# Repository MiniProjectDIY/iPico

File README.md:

# iPico
RP2350 based UF2 hardware security key

## Hardware

iPico use the same IO as official raspberry pi Pico2 board, just replaced physical push button with capacitive touch button on pcb and change usb connector from female to male.

## Firmware
Use  [pico-fido](https://github.com/polhenarejos/pico-fido/releases) firmware for pico 2 board will do.

## Enclosure

3d printed case using file from 3D folder,using M1.4* 2 heat inserts and M1.4*5 counter sink screws.

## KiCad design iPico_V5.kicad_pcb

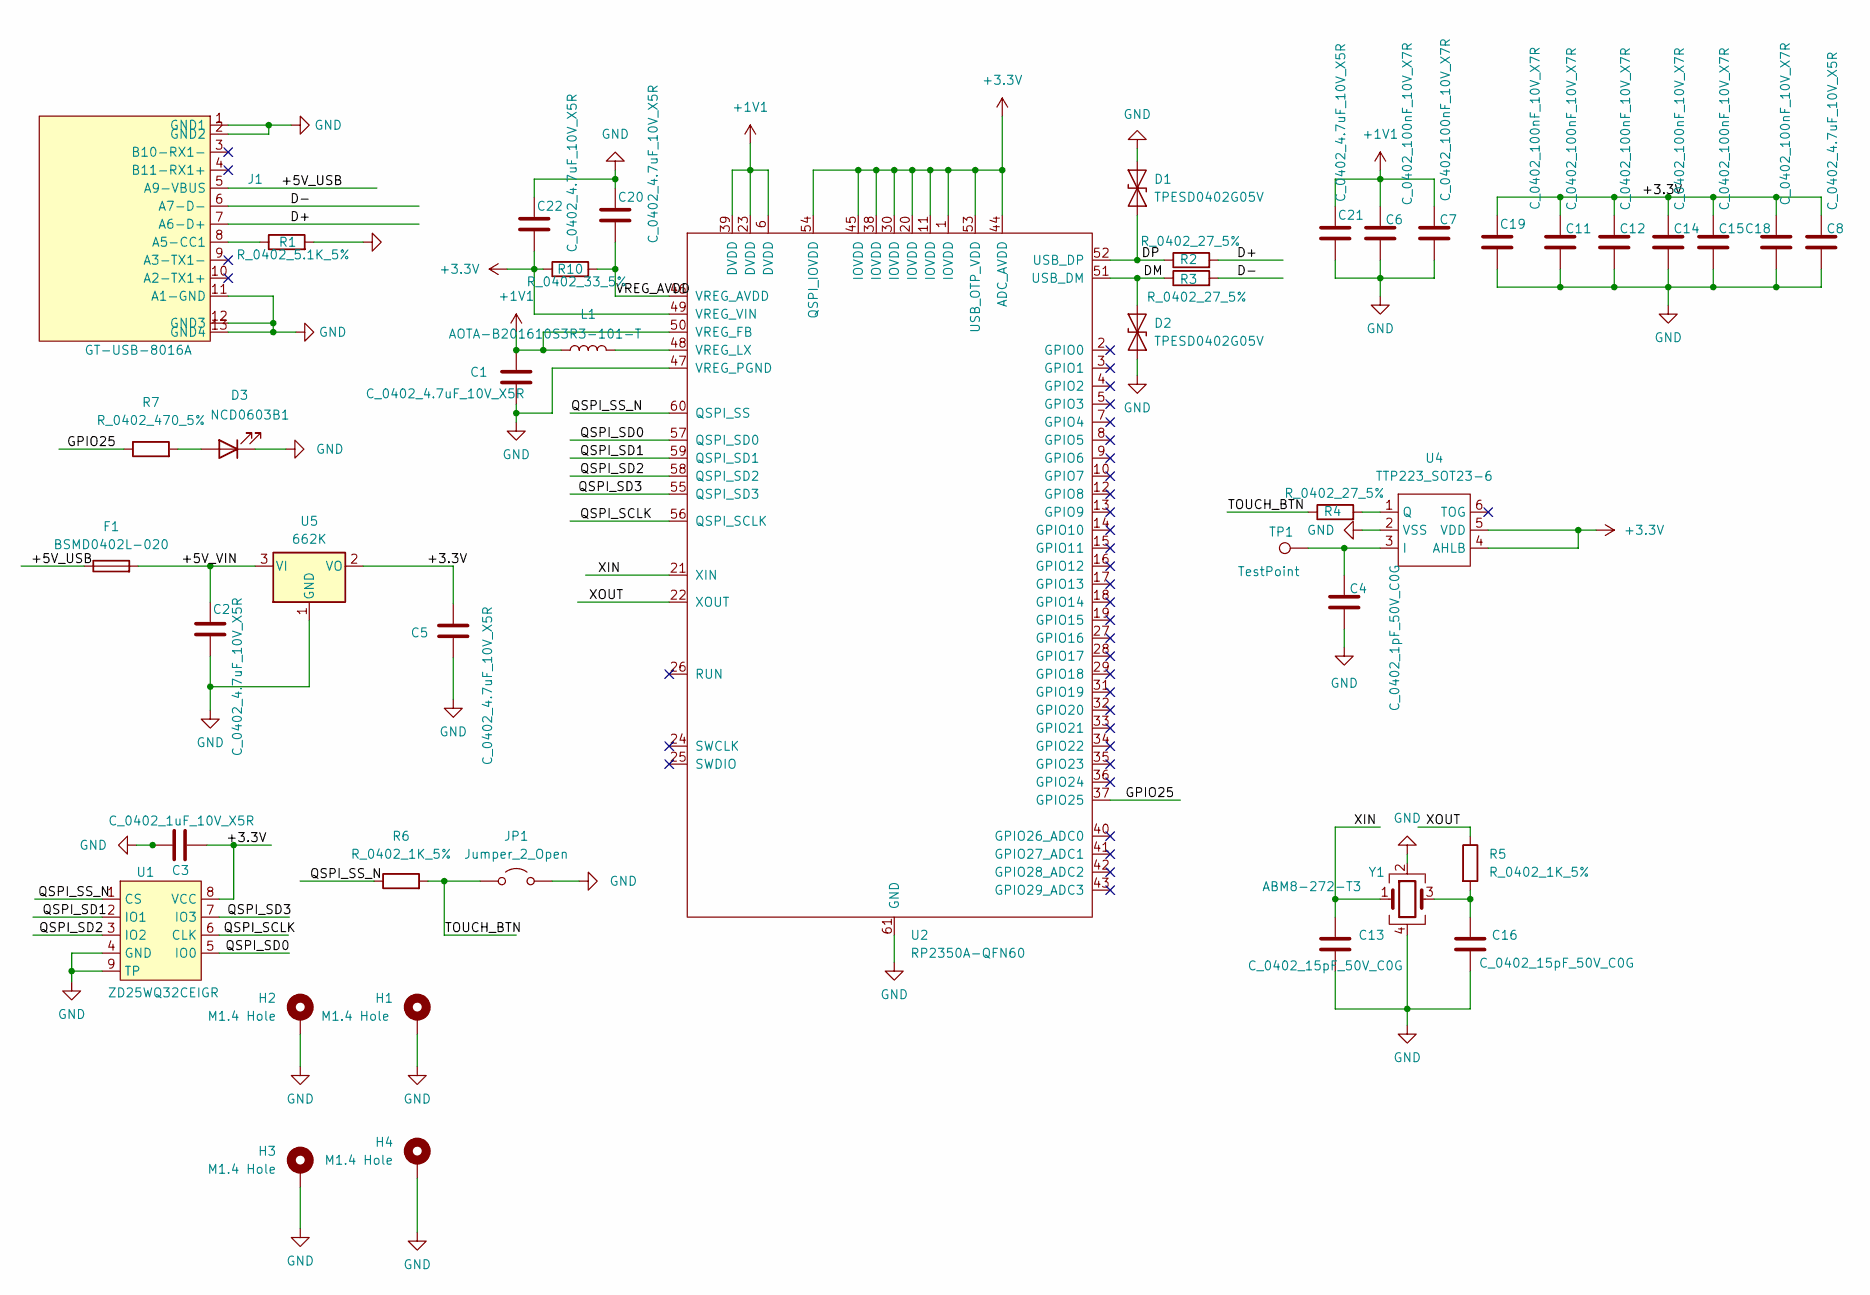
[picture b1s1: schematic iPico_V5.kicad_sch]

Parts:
C1, C2, C5, C8, C20, C21, C22: C_0402_4.7uF_10V_X5R; C_0402_1005Metric
C3: C_0402_1uF_10V_X5R; C_0402_1005Metric
C4: C_0402_1pF_50V_C0G; C_0402_1005Metric
C6, C7, C11, C12, C14, C15, C18, C19: C_0402_100nF_10V_X7R; C_0402_1005Metric
C13, C16: C_0402_15pF_50V_C0G; C_0402_1005Metric
D1, D2: TPESD0402G05V; R_0402_1005Metric
D3: NCD0603B1; LED_0603_1608Metric
F1: BSMD0402L-020; Fuse_0402_1005Metric
H1, H2, H3, H4: M1.4 Hole; MountingHole-M1.4
J1: GT-USB-8016A
JP1: Jumper_2_Open; SolderJumper-2_P1.3mm_Open_Pad1.0x1.5mm
L1: AOTA-B201610S3R3-101-T; LT_L0806
R1: R_0402_5.1K_5%; R_0402_1005Metric
R2, R3, R4: R_0402_27_5%; R_0402_1005Metric
R5, R6: R_0402_1K_5%; R_0402_1005Metric
R7: R_0402_470_5%; R_0402_1005Metric
R10: R_0402_33_5%; R_0402_1005Metric
TP1: TestPoint; TP_8MM
U1: ZD25WQ32CEIGR; USON8-2x3mm-EP0.2x1.6mm
U2: RP2350A-QFN60; RP2350A_QFN-60_EP_7.75x7.75_Pitch0.4mm
U4: TTP223_SOT23-6; SOT-23-6
U5: 662K; SOT-23
Y1: ABM8-272-T3; Crystal_SMD_2520-4Pin_2.5x2.0mm

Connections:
+1V1: C1.1, C6.1, C7.1, C21.2, L1.1, U2.6 (DVDD), U2.23 (DVDD), U2.39 (DVDD), U2.50 (VREG_FB)
+3.3V: C3.2, C5.1, C8.1, C11.1, C12.1, C14.1, C15.1, C18.1, C19.2, C22.1, R10.1, U1.8 (VCC), U2.1 (IOVDD), U2.11 (IOVDD), U2.20 (IOVDD), U2.30 (IOVDD), U2.38 (IOVDD), U2.44 (ADC_AVDD), U2.45 (IOVDD), U2.49 (VREG_VIN), U2.53 (USB_OTP_VDD), U2.54 (QSPI_IOVDD), U4.4 (AHLB), U4.5 (VDD), U5.2 (VO)
/+5V_USB: F1.1, J1.5 (A9-VBUS)
/+5V_VIN: C2.1, F1.2, U5.3 (VI)
/D+: J1.7 (A6-D+), R2.2
/D-: J1.6 (A7-D-), R3.2
/DM: D2.2 (A2), R3.1, U2.51 (USB_DM)
/DP: D1.1 (A1), R2.1, U2.52 (USB_DP)
/GPIO25: R7.1, U2.37 (GPIO25)
/QSPI_SCLK: U1.6 (CLK), U2.56 (QSPI_SCLK)
/QSPI_SD0: U1.5 (IO0), U2.57 (QSPI_SD0)
/QSPI_SD1: U1.2 (IO1), U2.59 (QSPI_SD1)
/QSPI_SD2: U1.3 (IO2), U2.58 (QSPI_SD2)
/QSPI_SD3: U1.7 (IO3), U2.55 (QSPI_SD3)
/QSPI_SS_N: R6.1, U1.1 (CS), U2.60 (QSPI_SS)
/TOUCH_BTN: JP1.1 (A), R4.1, R6.2
/VREG_AVDD: C20.1, R10.2, U2.46 (VREG_AVDD)
/XIN: C13.1, U2.21 (XIN), Y1.1
/XOUT: R5.1, U2.22 (XOUT)
GND: C1.2, C2.2, C3.1, C4.2, C5.2, C6.2, C7.2, C8.2, C11.2, C12.2, C13.2, C14.2, C15.2, C16.2, C18.2, C19.1, C20.2, C21.1, C22.2, D1.2 (A2), D2.1 (A1), D3.1 (K), H1.1, H2.1, H3.1, H4.1, J1.1 (GND1), J1.2 (GND2), J1.11 (A1-GND), J1.12 (GND3), J1.13 (GND4), JP1.2 (B), R1.2, U1.4 (GND), U1.9 (TP), U2.47 (VREG_PGND), U2.61 (GND), U4.2 (VSS), U5.1 (GND), Y1.2, Y1.4
unnamed: C16.1, R5.2, Y1.3
unnamed: D3.2 (A), R7.2
unnamed: J1.8 (A5-CC1), R1.1
unnamed: L1.2, U2.48 (VREG_LX)
unnamed: C4.1, TP1.1, U4.3 (I)
unnamed: R4.2, U4.1 (Q)

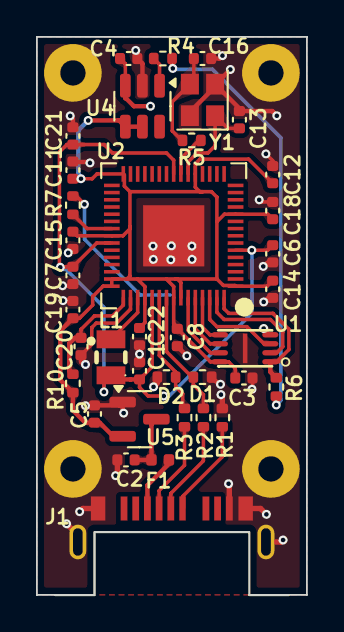
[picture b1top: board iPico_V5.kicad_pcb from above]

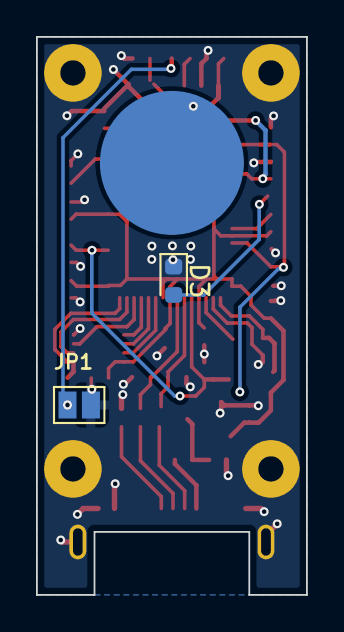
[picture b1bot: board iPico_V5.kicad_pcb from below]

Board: 2 copper layers, 15.0 x 31.0 mm, 44 parts (3 on the bottom side), 26 nets.

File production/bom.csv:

Designator,Footprint,Quantity,Value,LCSC Part #
C1,0402,1,C_0402_4.7uF_6.3V_X5R,
"C11, C12, C14, C15, C18, C19, C6, C7",0402,8,C_0402_100nF_10V_X7R,
"C13, C16",0402,2,C_0402_15pF_50V_C0G,
"C2, C5",0402,2,C_0402_10uF_10V_X5R,
"C20, C21, C22, C8",0402,4,C_0402_4.7uF_10V_X5R,
C3,0402,1,C_0402_1uF_10V_X5R,
C4,0402,1,C_0402_1pF_50V_C0G,
"D1, D2",0402,2,TPESD0402G05V,
D3,0402,1,NCD0402B1,
F1,0402,1,BSMD0402L-020,
"H1, H2, H3, H4",MountingHole-M1.4,4,MountingHole_Pad,
J1,GT-USB-8016A,1,GT-USB-8016A,
JP1,SolderJumper-2_P1.3mm_Open_Pad1.0x1.5mm,1,Jumper_2_Open,
L1,LT_L0806,1,AOTA-B201610S3R3-101-T,
R1,0402,1,R_0402_5.1K_5%,
R10,0402,1,R_0402_33_5%,
"R2, R3, R4",0402,3,R_0402_27_5%,
"R5, R6",0402,2,R_0402_1K_5%,
R7,0402,1,R_0402_470_5%,
U1,USON8-2x3mm-EP0.2x1.6mm,1,ZD25WQ32CEIGR,
U2,RP2350A_QFN-60_EP_7.75x7.75_Pitch0.4mm,1,RP2350A-QFN60,
U4,SOT-23-6,1,TTP223_SOT23-6,
U5,SOT-23,1,662K,
Y1,Crystal_SMD_2520-4Pin_2.5x2.0mm,1,ABM8-272-T3,

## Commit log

2025-04-19 V5 Initial
2025-04-19 add pico fido compile documents
